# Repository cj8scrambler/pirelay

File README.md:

pirelay
=======

pirelay is a small add-on board for the [Raspberry Pi](http://www.raspberrypi.org/) for up to 9 temperature controlled relays.  The board's relays are controlled by WS2801 LED drivers which allow for PWM output.  Each relay be a [small on circuit](http://www.allelectronics.com/make-a-store/item/SRLY-19/1A-SOLID-STATE-RELAY-3-8VDC-CONTROL/1.html) relay or a [larger off circuit SSR](http://www.allelectronics.com/make-a-store/item/SRLY-50/50-AMP-SOLID-STATE-RELAY/1.html).  A network of Maxim [One Wire Bus temperature sensors](http://www.maximintegrated.com/datasheet/index.mvp/id/2812) can be connected and assigned to each relay.  The temperature control algorithm can be set to PID, ON/OFF (with compressor delay) or manual mode.

All control and monitoring is done through a web interface.  Temperature and power output data is logged to an SQlite3 database for viewing history charts.

The board is designed for homebrew beer fermentation temperature control but can be easily adapted to other uses.  For beer fermentation a single chest freezer and up to 8 individual fermenters can be controlled from 1 pirelay.

Status
------
As of November 2013 the project is in an early development phase.  The 3rd version of the board ([v2.0d](http://oshpark.com/shared_projects/q5iLnXZY)) has been arrived, but needs to be assembled.  The basic framework of the code is in place to read temp sensors, control relays with PWM, log data to a database and provide a basic API for a more advanced web front end.

Still need to implement true PID mode, move configuration from hardcoding to web interface, build web interface for viewing historical data.

License
-------
The hardware schematic and layout files (Eagle PCB) are included in the repo and licensed under [CERN OHL v.1.1](http://ohwr.org/cernohl)

The software for pirelay is licensed under [Apache License, Version 2.0](http://www.apache.org/licenses/LICENSE-2.0.html)

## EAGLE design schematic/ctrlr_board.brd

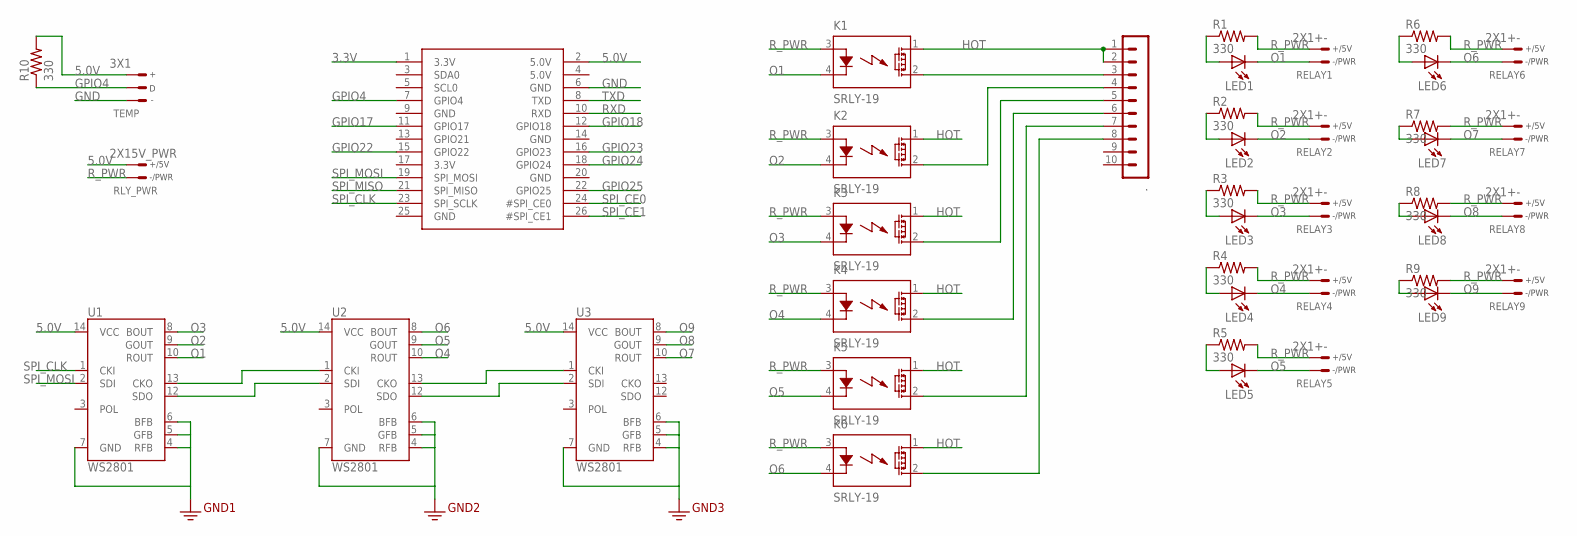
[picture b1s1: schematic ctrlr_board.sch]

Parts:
.: 10X1; HDR10
K1, K2, K3, K4, K5, K6: SRLY-19; OAC5
LED1, LED2, LED3, LED4, LED5, LED6, LED7, LED8, LED9: LED; LED0603
R1, R2, R3, R4, R5, R6, R7, R8, R9, R10: 330; R0603
RELAY1, RELAY2, RELAY3, RELAY4, RELAY5, RELAY6, RELAY7, RELAY8, RELAY9: 2X1+-; HDR2
RLY_PWR: 2X15V_PWR; HDR2_5V_PWR
RPI_HDR: RASPBERRY_PI_HEADERRASPI_HDR; RASPBERRY_PI_HEADER
TEMP: 3X1; HDR3
U1, U2, U3: WS2801; SOP-14

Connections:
3.3V: RPI_HDR.1 (3.3V)
5.0V: R10.2, RLY_PWR.+, RPI_HDR.2 (5.0V), TEMP.+, U1.14 (VCC), U2.14 (VCC), U3.14 (VCC)
GND: RPI_HDR.6 (GND), TEMP.-, U1.4 (RFB), U1.5 (GFB), U1.6 (BFB), U1.7 (GND), U2.4 (RFB), U2.5 (GFB), U2.6 (BFB), U2.7 (GND), U3.4 (RFB), U3.5 (GFB), U3.6 (BFB), U3.7 (GND)
GPIO4: R10.1, RPI_HDR.7 (GPIO4), TEMP.D
GPIO17: RPI_HDR.11 (GPIO17)
GPIO18: RPI_HDR.12 (GPIO18)
GPIO22: RPI_HDR.15 (GPIO22)
GPIO23: RPI_HDR.16 (GPIO23)
GPIO24: RPI_HDR.18 (GPIO24)
GPIO25: RPI_HDR.22 (GPIO25)
HOT: ..1, ..2, K1.1 (D1), K2.1 (D1), K3.1 (D1), K4.1 (D1), K5.1 (D1), K6.1 (D1)
unnamed: LED1.A, R1.1
unnamed: LED2.A, R2.1
unnamed: LED3.A, R3.1
unnamed: LED4.A, R4.1
unnamed: LED6.A, R6.1
unnamed: LED5.A, R5.1
unnamed: ..4, K2.2 (D2)
unnamed: ..5, K3.2 (D2)
unnamed: ..6, K4.2 (D2)
unnamed: ..7, K5.2 (D2)
unnamed: ..8, K6.2 (D2)
unnamed: ..3, K1.2 (D2)
unnamed: LED7.A, R7.1
unnamed: LED8.A, R8.1
unnamed: U1.13 (CKO), U2.1 (CKI)
unnamed: U1.12 (SDO), U2.2 (SDI)
unnamed: U2.12 (SDO), U3.2 (SDI)
unnamed: U2.13 (CKO), U3.1 (CKI)
unnamed: LED9.A, R9.1
O1: K1.4 (K), LED1.C, RELAY1.-, U1.10 (ROUT)
O2: K2.4 (K), LED2.C, RELAY2.-, U1.9 (GOUT)
O3: K3.4 (K), LED3.C, RELAY3.-, U1.8 (BOUT)
O4: K4.4 (K), LED4.C, RELAY4.-, U2.10 (ROUT)
O5: K5.4 (K), LED5.C, RELAY5.-, U2.9 (GOUT)
O6: K6.4 (K), LED6.C, RELAY6.-, U2.8 (BOUT)
O7: LED7.C, RELAY7.-, U3.10 (ROUT)
O8: LED8.C, RELAY8.-, U3.9 (GOUT)
O9: LED9.C, RELAY9.-, U3.8 (BOUT)
RXD: RPI_HDR.10 (RXD)
R_PWR: K1.3 (A), K2.3 (A), K3.3 (A), K4.3 (A), K5.3 (A), K6.3 (A), R1.2, R2.2, R3.2, R4.2, R5.2, R6.2, R7.2, R8.2, R9.2, RELAY1.+, RELAY2.+, RELAY3.+, RELAY4.+, RELAY5.+, RELAY6.+, RELAY7.+, RELAY8.+, RELAY9.+, RLY_PWR.-
SPI_CE0: RPI_HDR.24 (#SPI_CE0)
SPI_CE1: RPI_HDR.26 (#SPI_CE1)
SPI_CLK: RPI_HDR.23 (SPI_SCLK), U1.1 (CKI)
SPI_MISO: RPI_HDR.21 (SPI_MISO)
SPI_MOSI: RPI_HDR.19 (SPI_MOSI), U1.2 (SDI)
TXD: RPI_HDR.8 (TXD)

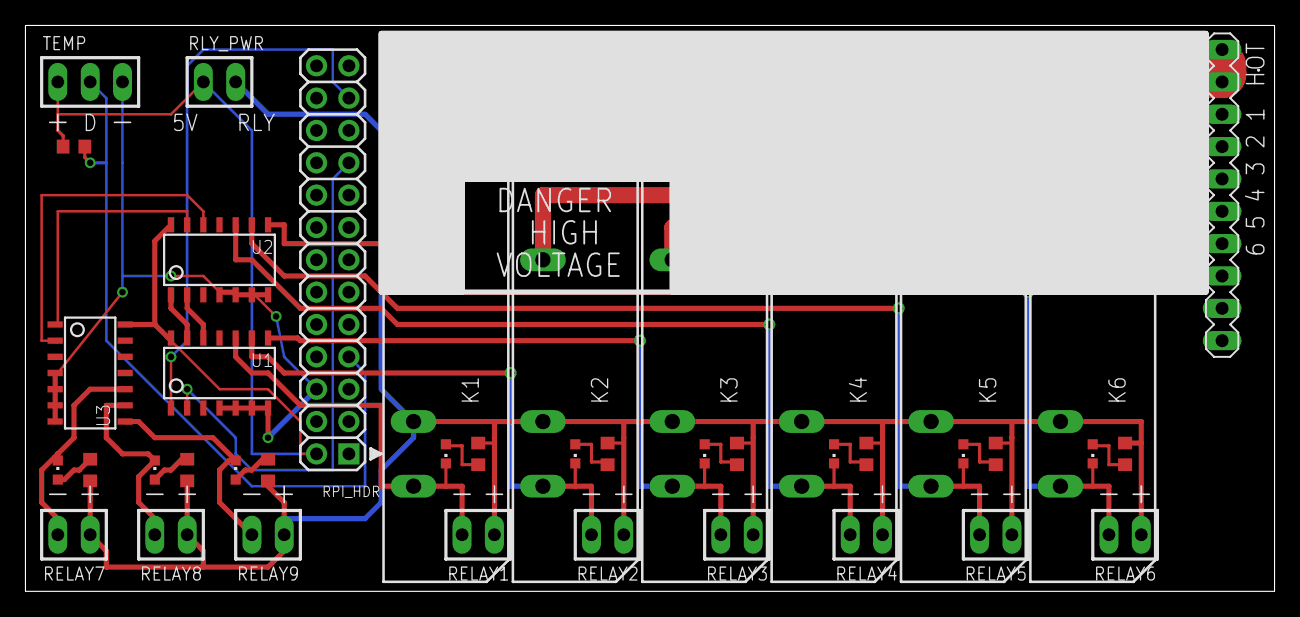
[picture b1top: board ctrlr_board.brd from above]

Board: 2 copper layers, 98.1 x 44.4 mm, 41 parts (0 on the bottom side), 35 nets.

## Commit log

2013-01-30 Populate the initial README on github
2013-02-20 Remove threading, add DB permissions check, enable httpd
    Moved to single thread to fix temp reading contention issues.
    PWM from software is not reliable even with a high priority thread,
    so it will need to move to hardware control. For now it's
    handled from the main thread which causes some latency when
    there is scheduling starvation like durring high load or I/O
    operations.
2013-04-02 1st pass implementation
    Initial Framework
    -makefile
    -spawn 3 threads
    *temp reader
    *output controller
    *data server
2013-04-02 Seperate timer signals and add system_settings
    Temp conversion is broken
2013-04-02 Add Eagle schematics
    Also rearrange files
2013-04-02 V1.0 of relay board
2013-04-02 Add HW tracking info file
2013-04-02 Expand temp readings, start implenting logging to SQL database
2013-04-02 Version 1.1 of expansion board
    * Rotated header 180 so expansion board sits over Rpi
    * re-wired relays to switch GND via darlingtons
    * Added optional SMD LEDs to relays 1-6 for testing
2013-04-02 Version 1.1b of expansion board
    * v. 1.1 failed batchpcb DRC.
    * Re-did layout by hand
    * Added larger solder pads on relays
2013-04-02 Version 1.1c of expansion board
    * v. 1.1b failed batchpcb DRC (SFE DRC rules were the problem)
2013-04-02 Basic logging implemented
    * Log to db
    * Moved from mysql to sqlite3 for performance
2013-04-02 Cleanup for migration to github
2013-06-20 Re-write output control for V2 hardware
    Move PWM output control from host software implementation to
    WS2801 LED driver chips which were added on V2 hardware.
2013-06-22 Framework added for REST API
    An empty framework was added for a RESTful API. This will be used
    by a web GUI (or other client) to configure, and monitor the system.
2013-06-23 Board updates for V2.0 hardware
    BatchPCB went out of business so switching to oshpark.com.
    Removed gerber files since they aren't needed there. V2.0 has
    the following changes:
    * Replace darlington array with 3 WS2801 to do PWM in hardware
    * Add 9th relay output
    * silkscreen high voltage area
2013-09-10 Implemented the GET calls for /node URIs in the data handler
2013-11-26 Support for non Raspberry Pi machines
    Add support for building and running on any linux machine, not just
    Raspberry Pi hardware. Since the relay hardware can't exist on a PC,
    no valid data will be received or logged. However, this allows work
    on the UI and interface APIs.
    * Upgrade libbcm2835 to v. 1.33
    * libbcm2835: Skip SPI functions in debug mode

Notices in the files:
parts and their libraries:
SparkFun-DigitalIC: Licensing: CC v3.0 Share-Alike You are welcome to use this library for commercial purposes.
